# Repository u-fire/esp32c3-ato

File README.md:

# ESP32-C3-MINI-1U-N4

📒 [Datasheet](https://www.espressif.com/sites/default/files/documentation/esp32-c3-mini-1_datasheet_en.pdf)

This repository is an [atopile](https://atopile.io/) module for the ESP32-C3-MINI-*, a system-on-chip ESP32 WiFi/BLE chip. 
- external antenna connector (ESP32-C3-MINI-1U-N4) or PCB antenna (ESP32-C3-MINI-1-N4)
- RISC­V single­core microprocessor
- 4 MB flash in chip package
- 15 GPIOs
- integrated USB controller

## 🏁 Get started
### Installation
From inside a project directory terminal: `ato install esp32c3-ato`

### Code
```vb
from "esp32c3-ato/esp32c3.ato" import ESP32C3_EXT_ANT
# - or -
from "esp32c3-ato/esp32c3.ato" import ESP32C3_PCB_ANT

from "generics/interfaces.ato" import Power
from "generics/interfaces.ato" import UART
from "generics/interfaces.ato" import USB2

module Esp:
    vdd3v3 = new Power
    uart = new UART
    usb = new USB2

    esp_ext = new ESP32C3_EXT_ANT   # external antenna connector
    esp_ext.power ~ vdd3v3
    esp_ext.uart ~ uart
    esp_ext.usb ~ usb

    # - or -
    
    esp_pcb = new ESP32C3_PCB_ANT   # PCB antenna
    esp_pcb.power ~ vdd3v3
    esp_pcb.uart ~ uart
    esp_pcb.usb ~ usb
```
*GPIO pins are available as IO0 - IO19*

## 🤔 Design Considerations
This is a minimal circuit:
- to use the USB lines to spec, you'll need to add your own resistors and capacitors per Figure 7, pg 25 of the datasheet
- there's no crystal in this design, it is required for light-sleep mode

## ⚡ Programming
The ESP32-C3 can have firmware uploaded with just a USB cable. No additional hardware is required, although this method *isn't the best approach for a smooth development experience.*
### Connections
You'll need a USB breakout board or other means to access the cables and a 3.3 volt power source, not the 5 volt USB line. Tie all grounds together. 

|ESP| | USB| |3V3
|-------:|:-:|:---:|:-:|:---|
| ESP.D+ 🟨|~| 🟨 USB.D+||
| ESP.D- 🟦|~| 🟦 USB.D-||
| *ESP.VCC* 🟥|~||~|🟥 *3V3.VCC*|
|**ESP.GND**⬛ |~| ⬛ **USB.GND** ⬛|~|⬛ **3V3.GND**|

### Procedure
1. Reset the chip while IO9 is LOW.
    - a reset can be accomplished by a power-cycle, or bringing the EN pin LOW then HIGH
2. Upload the firmware
3. Return IO9 to its default HIGH state
4. Power-cycle the chip to run normally

### Arduino and PlatformIO
#### Arduino
- follow [Espressif's instructions](https://docs.espressif.com/projects/arduino-esp32/en/latest/installing.html) for adding ESP32 support. 
- choose `ESP32C3 Dev Module` from the list
    - use `USBSerial` instead of `Serial` if using the same USB cable as you did for firmware upload

#### PlatformIO
```ini
[env:esp32-c3-devkitm-1]
platform = espressif32
board = esp32-c3-devkitm-1
```

## 🙏 Contributing
This design is intended to be a community best-effort at a minimal circuit combining:
- datasheet reference design
- readily available components
- modular and reusable layout

You are greatly encouraged to contribute or discuss any improvements here so that everyone may benefit. 

## License
[CERN-OHL-P v2](https:/cern.ch/cern-ohl)

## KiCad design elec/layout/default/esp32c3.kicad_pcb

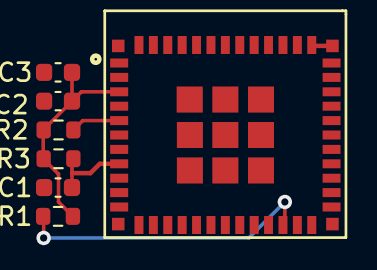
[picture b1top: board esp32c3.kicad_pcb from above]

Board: 2 copper layers, 7 parts (0 on the bottom side), 5 nets.

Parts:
C1: 50V 1uF X5R ±10% 0603 Multilayer Ceramic Capacito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; C0603
C2: 10V 10uF X5R ±10% 0603 Multilayer Ceramic Capacit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; C0603
C3: 50V 100nF X7R ±10% 0603 Multilayer Ceramic Capaci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; C0603
R1, R2, R3: 100mW Thick Film Resistors ±100ppm/℃ ±1% 10kΩ 060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; R0603
U1: WIFIM-SMD_61P-L13.2-W12.5-P0.80

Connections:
en: C1.1, R3.2, U1.8
gnd: C1.2, C2.2, C3.2, U1.1, U1.2, U1.11, U1.14, U1.36, U1.37, U1.38, U1.39, U1.40, U1.41, U1.42, U1.43, U1.44, U1.45, U1.46, U1.47, U1.48, U1.49, U1.50, U1.51, U1.52, U1.53, U1.54, U1.55, U1.56, U1.57, U1.58, U1.59, U1.60, U1.61
io2: R2.1, U1.5
io8: R1.1, U1.22
vcc: C2.1, C3.1, R1.2, R2.2, R3.1, U1.3

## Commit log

2024-02-16 Initial
2024-02-19 import changes
2024-03-11 added signals to GPIO
2024-03-14 Both variants added
    External antenna and PCB antenna variants usable from this package.
